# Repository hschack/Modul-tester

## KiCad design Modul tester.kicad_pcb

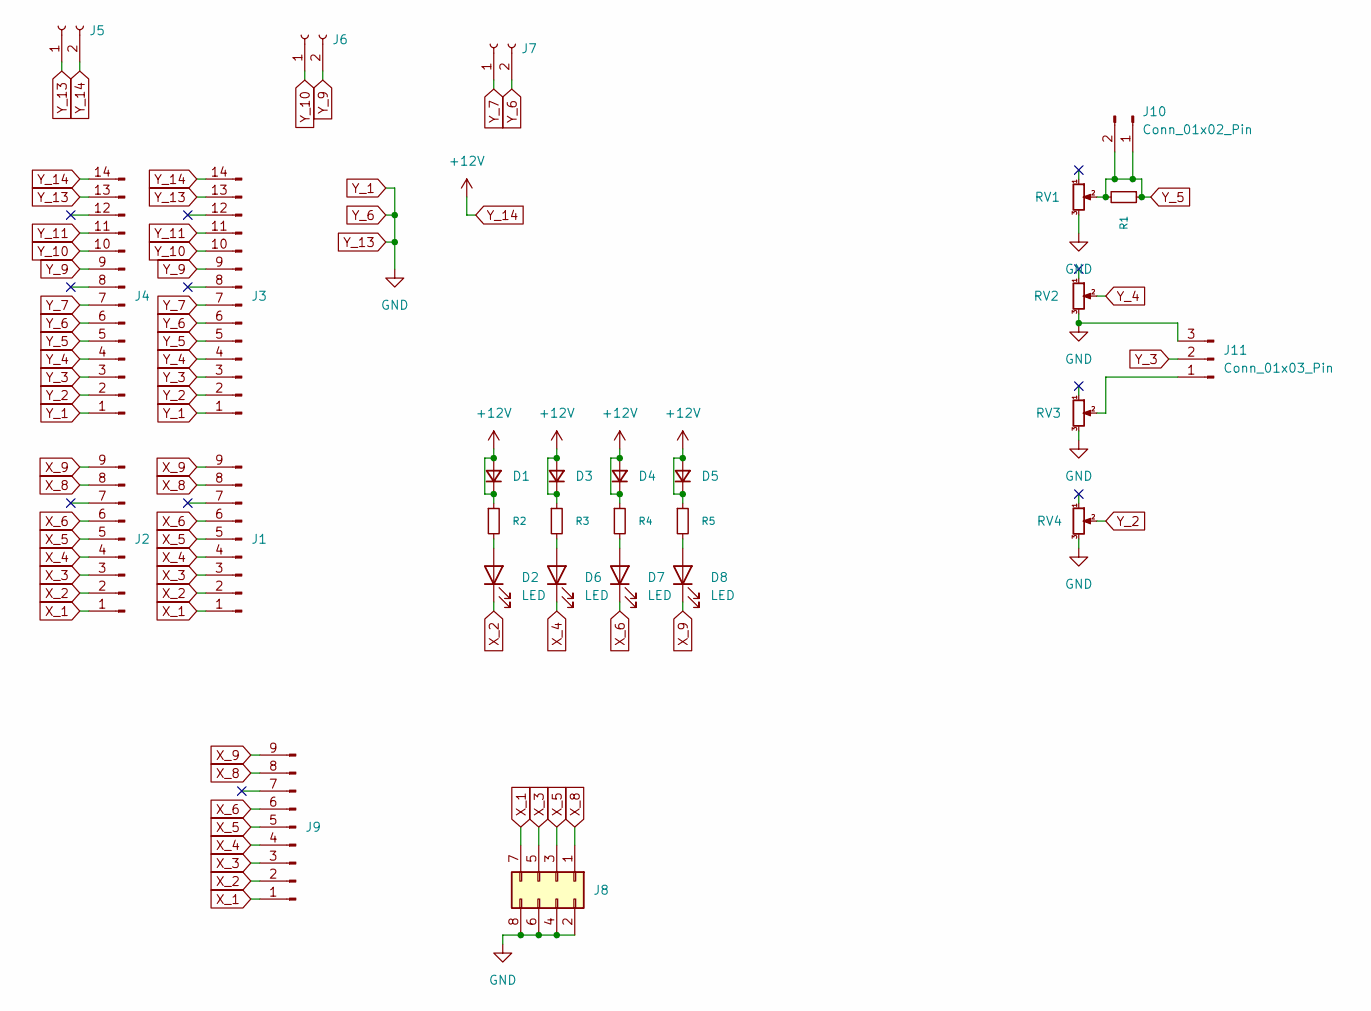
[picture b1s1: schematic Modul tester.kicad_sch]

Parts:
D1, D3, D4, D5: D_Small; D_MiniMELF
D2, D6, D7, D8: LED; LED_0805_2012Metric
J1, J2, J9: Conn_01x09_Pin; PhoenixContact_MCV_1,5_9-G-5.08_1x09_P5.08mm_Vertical
J3, J4: Conn_01x14_Pin; PinHeader_1x14_P2.54mm_Vertical
J5, J6, J7: Conn_01x02_Socket; PhoenixContact_MCV_1,5_2-G-3.5_1x02_P3.50mm_Vertical
J8: Conn_02x04_Odd_Even; PinHeader_2x04_P2.54mm_Vertical
J10: Conn_01x02_Pin; PinHeader_1x02_P2.54mm_Vertical
J11: Conn_01x03_Pin; PinHeader_1x03_P2.54mm_Vertical
R1, R2, R3, R4, R5: R_Small; R_0805_2012Metric
RV1, RV2, RV3, RV4: R_Potentiometer_Small; Potentiometer_Alps_RK09K_Single_Vertical

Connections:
unnamed: D2.2 (A), R2.2
unnamed: D6.2 (A), R3.2
unnamed: D7.2 (A), R4.2
unnamed: D8.2 (A), R5.2
unnamed: J11.1, RV3.2
X_1: J1.1, J2.1, J8.7, J9.1
X_2: D2.1 (K), J1.2, J2.2, J9.2
X_3: J1.3, J2.3, J8.5, J9.3
X_4: D6.1 (K), J1.4, J2.4, J9.4
X_5: J1.5, J2.5, J8.3, J9.5
X_6: D7.1 (K), J1.6, J2.6, J9.6
X_8: J1.8, J2.8, J8.1, J9.8
X_9: D8.1 (K), J1.9, J2.9, J9.9
Y_1: J3.1, J3.6, J3.13, J4.1, J4.6, J4.13, J5.1, J7.2, J8.2, J8.4, J8.6, J8.8, J11.3, RV1.3, RV2.3, RV3.3, RV4.3
Y_2: J3.2, J4.2, RV4.2
Y_3: J3.3, J4.3, J11.2
Y_4: J3.4, J4.4, RV2.2
Y_5: J3.5, J4.5, J10.1, J10.2, R1.1, R1.2, RV1.2
Y_7: J3.7, J4.7, J7.1
Y_9: J3.9, J4.9, J6.2
Y_10: J3.10, J4.10, J6.1
Y_11: J3.11, J4.11
Y_14: D1.1 (K), D1.2 (A), D3.1 (K), D3.2 (A), D4.1 (K), D4.2 (A), D5.1 (K), D5.2 (A), J3.14, J4.14, J5.2, R2.1, R3.1, R4.1, R5.1

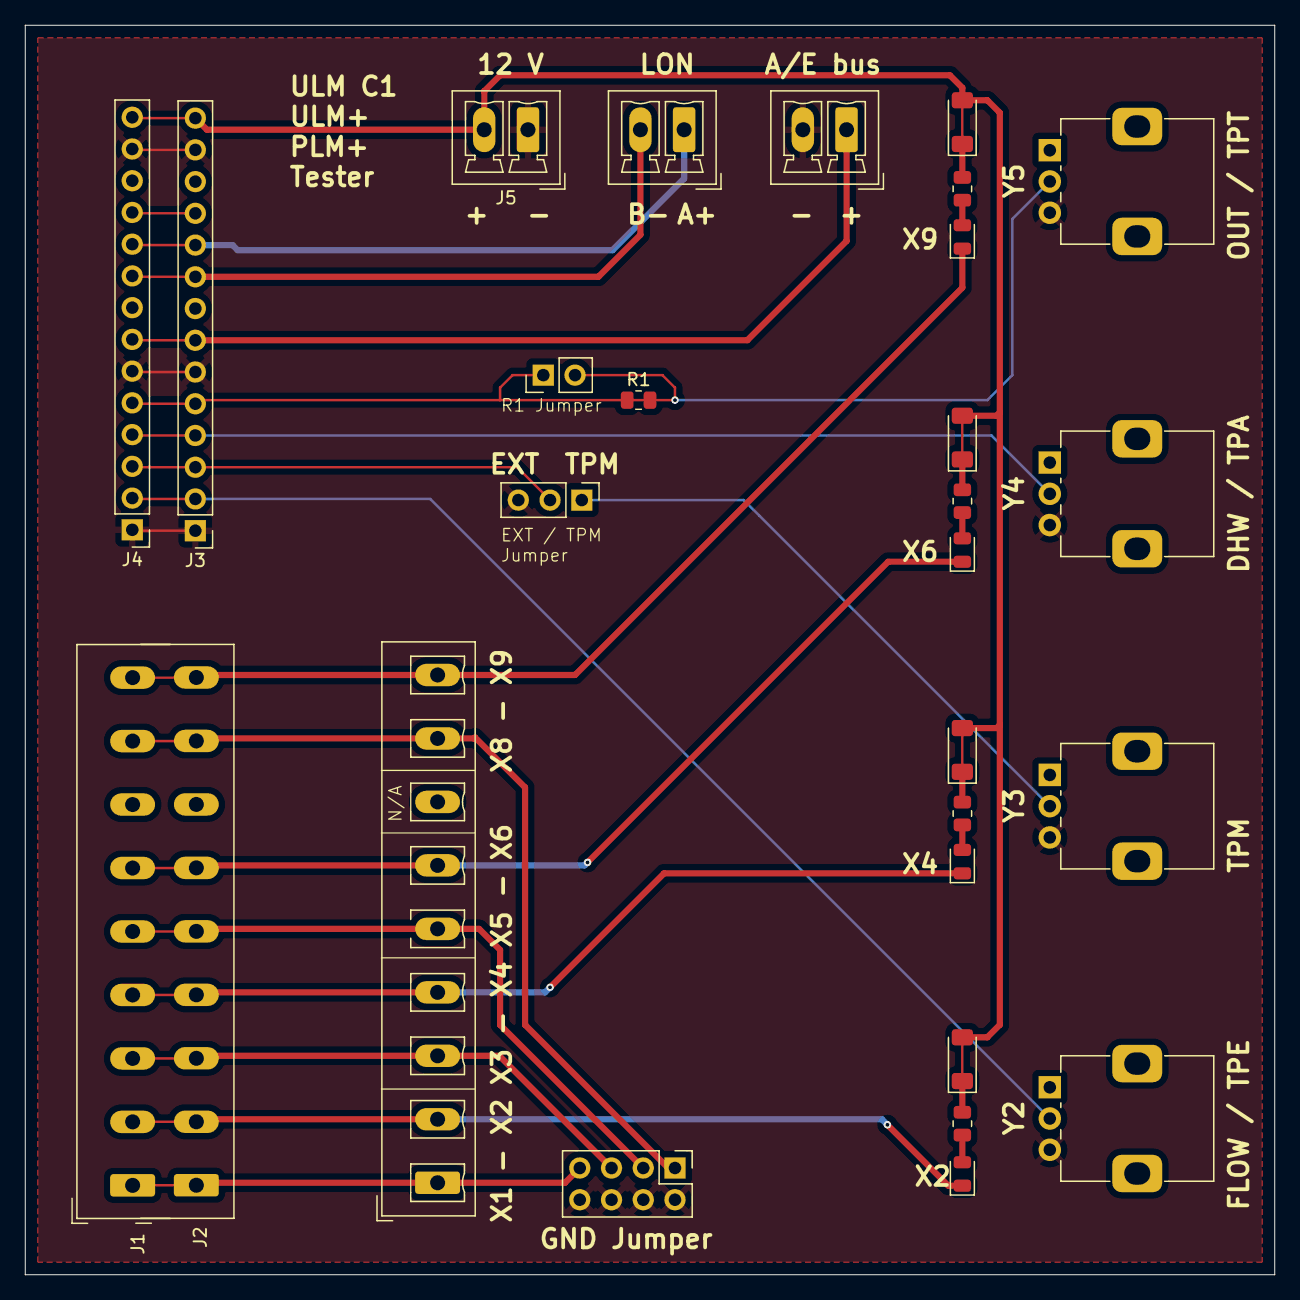
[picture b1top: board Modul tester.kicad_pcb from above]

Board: 2 copper layers, 100.0 x 100.0 mm, 28 parts (0 on the bottom side), 23 nets.
